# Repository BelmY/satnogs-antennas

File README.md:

# SatNOGS Antennas

Antennas for SatNOGS project

More information can be found in our [documentation](https://satnogs.org/documentation/hardware/).

## What's here?

### Helical antenna designs

* `Helical/UHC lhcp-version_1` is version 1 of our Helical antenna design.  It's
  a left-hand circularly polarized (LHCP) antenna, and requires only
  3D-printed parts (no CNC milling or laser-cutting required).

* `Helical/UHF-434-8-version_4` is version 4 of our Helical antenna design, an
  8-turn Helix that can be made in either left- or right-hand
  circularly polarized (RHCP) configurations.  It requires a laser cutter or
  water jet cutter for the plexiglass/polycarbonate supports, but is
  more rigid than version 1.

* `Helical/UHF-435-8-version_5` is version 5 of the Helical antenna
  design; it comes in RHCP configuration.  The supports are made from
  aluminum, and will require a drill press.

## License

&copy; 2014-2015 [Libre Space Foundation](http://librespacefoundation.org).

Licensed under the [CERN OHLv1.2](LICENSE).

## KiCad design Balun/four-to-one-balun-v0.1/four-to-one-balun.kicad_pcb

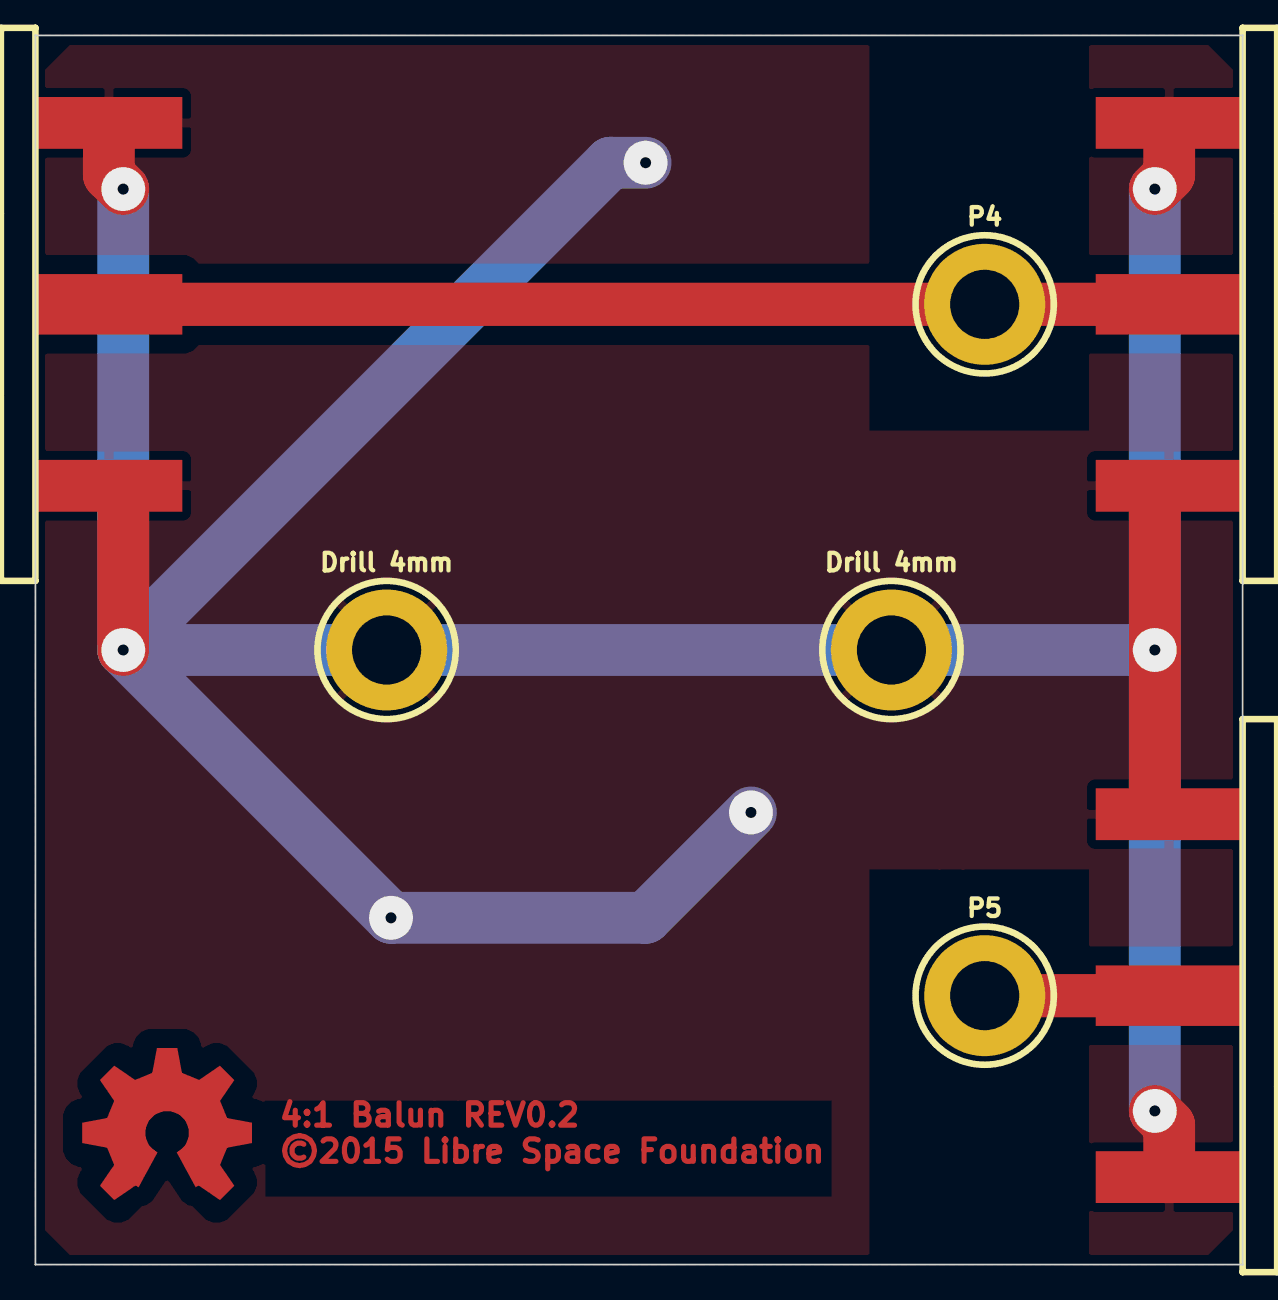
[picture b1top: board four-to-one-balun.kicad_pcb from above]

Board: 2 copper layers, 69.8 x 71.1 mm, 8 parts (0 on the bottom side), 3 nets.

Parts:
Drill 4mm, Drill 4mm#2: P***; DRILL_4mm
OSHW_COPPER_10MM: VAL**; OSHW_COPPER_10MM
P1, P2, P3: N-TYPE; NTYPE_EDGE
P4, P5: CLAMP; DRILL_4mm

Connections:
GND: Drill 4mm.1, Drill 4mm#2.1, P1.2, P2.2, P3.2
unnamed: P3.1, P5.1
unnamed: P1.1, P2.1, P4.1

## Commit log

2014-04-13 Yagi element to mast mounting bracket
2014-04-13 Code clean up and new stls
2014-04-13 T-connector and refactored code for axis mount
2014-04-13 STL files of the tracking box system.
2014-04-15 made axis hole smaller and added holes for screws
2014-04-15 added box axis bushing file
2014-04-15 corrected axis bushing file to fit in box
2014-04-15 enlarged bushing and axis large axis diameter
2014-04-20 Tripod and yagi antenna holders
2014-04-22 Add assemply blender filles .gitignore and how to blend and pics
2014-04-23 added antenna axs joint.stl file
2014-05-10 New antenna axis mount
2014-05-10 Manifold fix
2014-05-10 Turnstile antenna mount
2014-08-20 v0.1 source initial and final commit
2014-08-20 v0.2 source initial commit
2014-08-20 LNA housing
2014-08-20 Fixing spelling
2014-09-24 Ground Station Tracking v2
2014-09-24 Update BOM with links to STLs.
2014-09-24 Update Antenna directories.
2014-09-24 Updated BOM.
2014-09-28 New Helical antenna UHF lhcp.
2014-09-28 Add BOM of helical antenna UHF-lhcp.
2014-09-29 Add v2 of Tripod.
2014-10-04 Add axis_bushing source file.
2014-10-04 Add Axis Gear Spacer for v2.
2014-10-22 Add BOM for tripod v2
2014-10-24 Radome v1 added.
2014-10-26 Add all files for the diplexer schematic and pcb design
2014-10-27 Add Diplexer BOM.
2014-10-27 Update STL for Radome.
2014-10-27 Add Radome BOM.
2014-10-28 Update trakcer BOM.
2015-01-09 Add pockets for nuts at the axis_side part and update the stl file to
2015-01-18 Adding new yagi VHF v2
2015-01-18 Adding pdfs of Yagi VHF v2.
2015-02-05 New VHF v3 6element design.
2015-02-05 New UHF v1 10 elements design.
2015-03-08 Optimizing sensor holder for printability.
2015-03-08 Add source file and binary for homing ring.
2015-03-08 Modified axis gear ring in order to reduce friction.
2015-03-11 Change gitignore to ignore freecad backup files
2015-03-11 Add 3D printed cable hook to manage cables inside box
2015-03-11 Modify axis_bushing to be able to hold 2 ISO 3601 Size:026 o-rings on each side (for the 32mm diameter tube) to prevent water from licking in the box.
2015-04-14 Cleanup antennas repository.
2015-04-24 Update README with license notice
2015-04-27 Update documentation link
2015-05-08 First release of 4:1 balun PCB
2015-05-08 four-to-one-balun: Center schematic to page frame
2015-05-09 Fix connector obstruction to antenna elements
2015-06-13 nec2: GNU Octave antenna wavelength calculator
2015-06-13 nec2: Numerical electromagnetics code model for 6-element Yagi-Uda antenna
2015-06-13 nec2: Use V, H and total axis gain
2015-06-13 nec2: Fix phi range
2015-06-13 nec2: Add SatNOGS 6-element Yagi-Uda NEC2 output
2015-06-13 nec2: Radiation pattern, gain and SWR charts for SatNOGS 6-element Yagi-Uda antenna
2015-06-13 nec2: Code refactoring, print actual size, scale to tune at 145MHz
2015-06-13 nec2: Update cards with new wavelength and re-run simulation
2015-06-13 nec2: Update radiation pattern, SWR and gain charts
2015-06-13 nec2: Calculate sizes and distances for 8mm diameter elements
2015-06-13 nec2: Update cards with new wavelength after element diameter change
2015-06-13 nec2: Remove simulation output from repository
2015-06-13 nec2: Update radiation pattern and gain/SWR/impedance plots with results from new simulation
2015-06-13 Fix 6-element Yagi/Uda sloped elements
2015-06-13 nec2: Add GNU octave calculator and NEC2 file for 10-element Yagi/Uda UHF antenna
2015-06-13 nec2: Add GNU octave calculator and NEC2 file for 11-element Yagi/Uda UHF antenna
2015-06-13 Rename directory 'nec2' to 'NEC'
2015-09-01 Remove 'Balun' directory; four-to-one-balun has its own repository now at https://github.com/satnogs/four-to-one-balun/
2016-02-23 New directory for UHF Helical 434-8
2016-02-23 Designs for UHF Helical antenna in 434 MHz - 8 turns
2016-12-06 Folder for 435-8 helical design.
2017-10-15 Begin documenting what antenna versions are in the repo
2017-11-03 Add explanation of what's in this directory
    Source: https://satnogs.dozuki.com/Guide/Helical+Antenna+v4/11
2017-11-13 Incorporate versions in directory names
2017-11-13 Update README files with version names and links to assembly
2020-02-16 Add Libre Space Foundation Contribution Guide
2020-02-17 Fix license file to match original text version

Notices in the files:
Balun/four-to-one-balun-v0.1/four-to-one-balun.kicad_pcb:
©2015 Libre Space Foundation
